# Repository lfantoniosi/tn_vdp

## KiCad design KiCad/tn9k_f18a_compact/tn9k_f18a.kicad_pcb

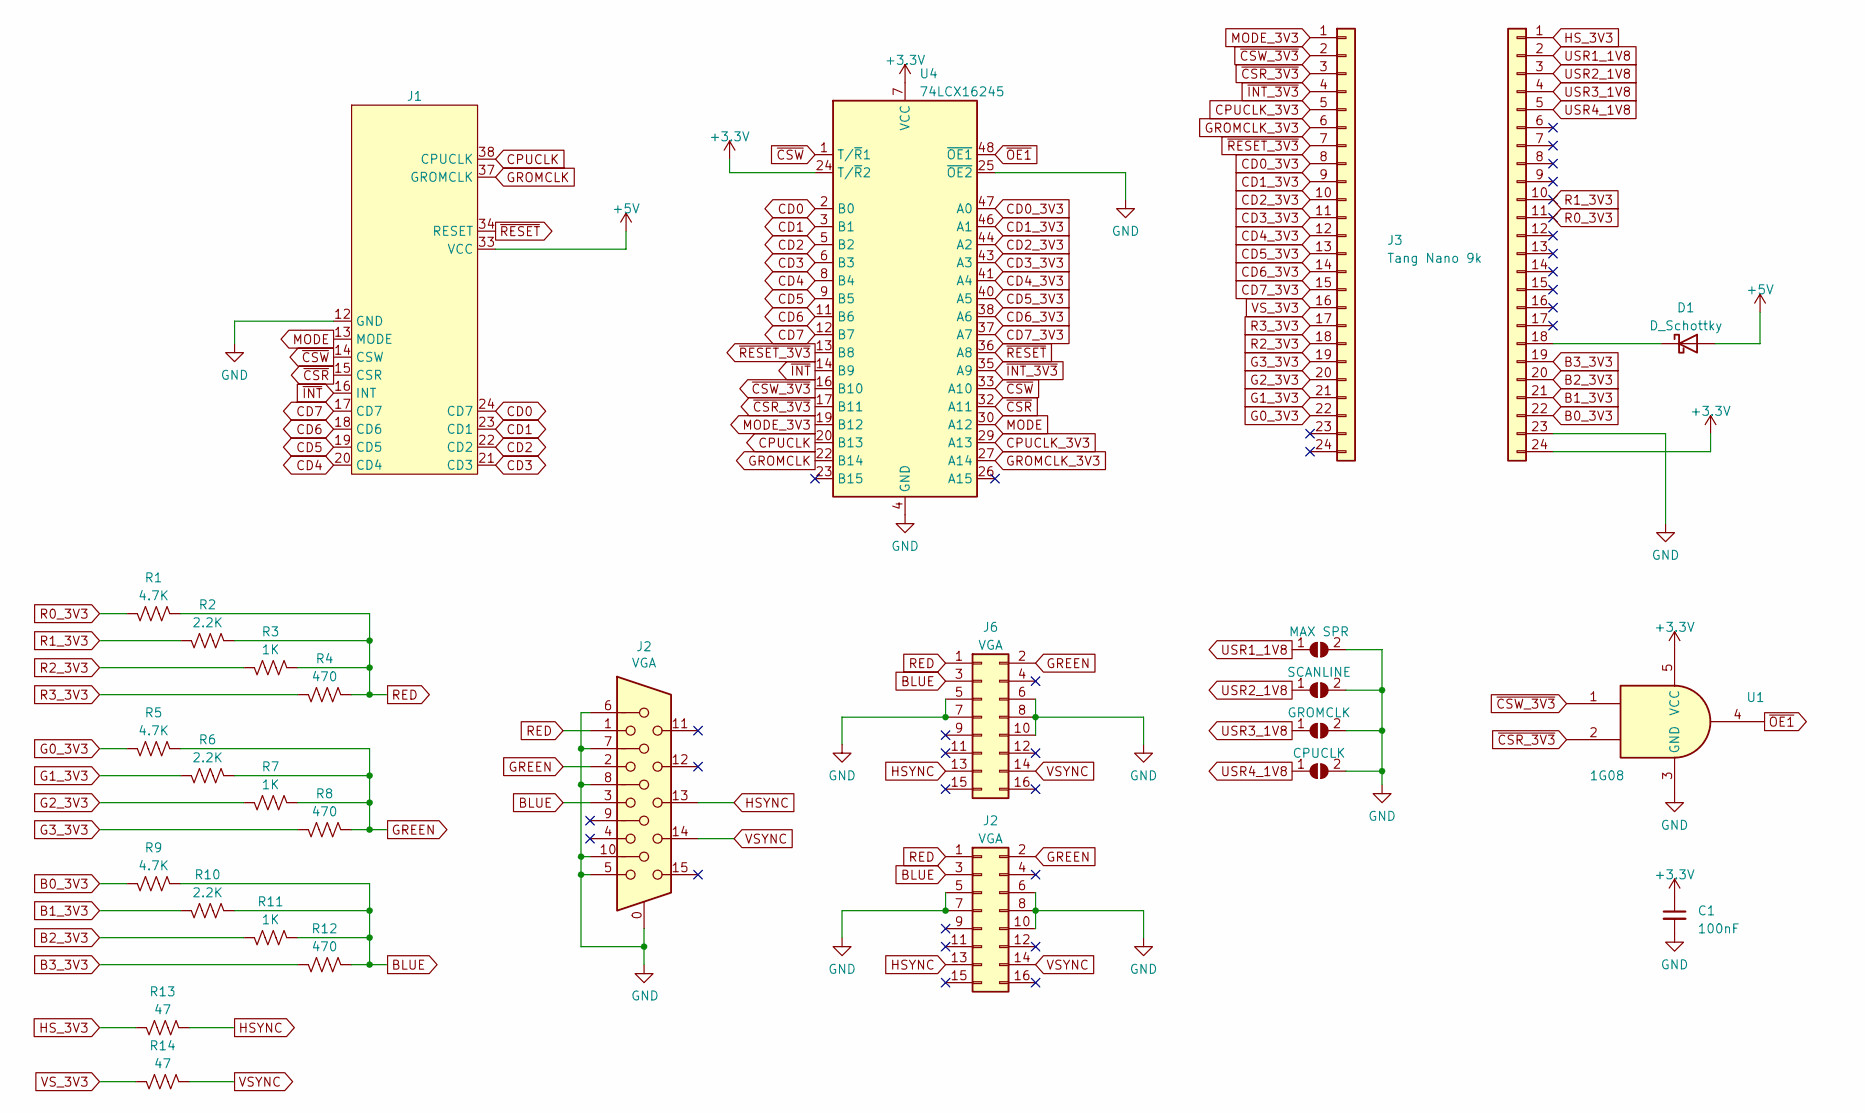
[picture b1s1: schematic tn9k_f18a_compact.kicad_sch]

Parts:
C1: 100nF; C_0603_1608Metric_Pad1.08x0.95mm_HandSolder
D1: D_Schottky; D_SOD-123
J1: TMS99xxA_Replacement
J2: VGA; DSUB-15-HD_Female_Horizontal_P2.29x1.98mm_EdgePinOffset3.03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
J3: Tang Nano 9k; PinSocket_1x24_P2.54mm_Vertical
J4: TN9k/2; PinSocket_1x24_P2.54mm_Vertical
J6: VGA; PinHeader_2x08_P2.54mm_Vertical
JP1: MAX SPR; SolderJumper-2_P1.3mm_Open_RoundedPad1.0x1.5mm
JP2: SCANLINE; SolderJumper-2_P1.3mm_Open_RoundedPad1.0x1.5mm
JP3: GROMCLK; SolderJumper-2_P1.3mm_Open_RoundedPad1.0x1.5mm
JP4: CPUCLK; SolderJumper-2_P1.3mm_Open_RoundedPad1.0x1.5mm
R1, R5, R9: 4.7K; R_0603_1608Metric_Pad0.98x0.95mm_HandSolder
R2, R6, R10: 2.2K; R_0603_1608Metric_Pad0.98x0.95mm_HandSolder
R3, R7, R11: 1K; R_0603_1608Metric_Pad0.98x0.95mm_HandSolder
R4, R8, R12: 470; R_0603_1608Metric_Pad0.98x0.95mm_HandSolder
R13, R14: 47; R_0603_1608Metric_Pad0.98x0.95mm_HandSolder
U1: 1G08; SOT-23-5_HandSoldering
U4: 74LCX16245; TSSOP-48_6.1x12.5mm_P0.5mm

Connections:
+3.3V: C1.1, J4.24, U1.5 (VCC), U4.7 (VCC), U4.18 (VCC), U4.24 (T/~R2), U4.31 (VCC), U4.42 (VCC)
+5V: D1.1 (K), D1.2 (A), J1.33 (VCC), J4.18
B0_3V3: J4.22, R9.2
B1_3V3: J4.21, R10.2
B2_3V3: J4.20, R11.2
B3_3V3: J4.19, R12.2
BLUE: J2.3, J6.3, R9.1, R10.1, R11.1, R12.1; also elsewhere on the board
CD0: J1.24 (CD7), U4.2 (B0)
CD0_3V3: J3.8, U4.47 (A0)
CD1: J1.23 (CD1), U4.3 (B1)
CD1_3V3: J3.9, U4.46 (A1)
CD2: J1.22 (CD2), U4.5 (B2)
CD2_3V3: J3.10, U4.44 (A2)
CD3: J1.21 (CD3), U4.6 (B3)
CD3_3V3: J3.11, U4.43 (A3)
CD4: J1.20 (CD4), U4.8 (B4)
CD4_3V3: J3.12, U4.41 (A4)
CD5: J1.19 (CD5), U4.9 (B5)
CD5_3V3: J3.13, U4.40 (A5)
CD6: J1.18 (CD6), U4.11 (B6)
CD6_3V3: J3.14, U4.38 (A6)
CD7: J1.17 (CD7), U4.12 (B7)
CD7_3V3: J3.15, U4.37 (A7)
CPUCLK: J1.38 (CPUCLK), U4.20 (B13)
CPUCLK_3V3: J3.5, U4.29 (A13)
G0_3V3: J3.22, R5.2
G1_3V3: J3.21, R6.2
G2_3V3: J3.20, R7.2
G3_3V3: J3.19, R8.2
GND: C1.2, J1.12 (GND), J2.0, J2.5, J2.6, J2.7, J2.8, J2.10, J4.23, J6.5, J6.6, J6.7, J6.8, J6.10, JP1.2 (B), JP2.2 (B), JP3.2 (B), JP4.2 (B), U1.3 (GND), U4.4 (GND), U4.10 (GND), U4.15 (GND), U4.21 (GND), U4.25 (~OE2), U4.28 (GND), U4.34 (GND), U4.39 (GND), U4.45 (GND); also elsewhere on the board
GREEN: J2.2, J6.2, R5.1, R6.1, R7.1, R8.1; also elsewhere on the board
GROMCLK: J1.37 (GROMCLK), U4.22 (B14)
GROMCLK_3V3: J3.6, U4.27 (A14)
HSYNC: J2.13, J6.13, R13.1; also elsewhere on the board
HS_3V3: J4.1, R13.2
MODE: J1.13 (MODE), U4.30 (A12)
MODE_3V3: J3.1, U4.19 (B12)
R0_3V3: J4.11, R1.2
R1_3V3: J4.10, R2.2
R2_3V3: J3.18, R3.2
R3_3V3: J3.17, R4.2
RED: J2.1, J6.1, R1.1, R2.1, R3.1, R4.1; also elsewhere on the board
USR1_1V8: J4.2, JP1.1 (A)
USR2_1V8: J4.3, JP2.1 (A)
USR3_1V8: J4.4, JP3.1 (A)
USR4_1V8: J4.5, JP4.1 (A)
VSYNC: J2.14, J6.14, R14.1; also elsewhere on the board
VS_3V3: J3.16, R14.2
~CSR_3V3: J3.3, U1.2, U4.17 (B11)
~CSR: J1.15 (CSR), U4.32 (A11)
~CSW_3V3: J3.2, U1.1, U4.16 (B10)
~CSW: J1.14 (CSW), U4.1 (T/~R1), U4.33 (A10)
~INT_3V3: J3.4, U4.35 (A9)
~INT: J1.16 (INT), U4.14 (B9)
~OE1: U1.4, U4.48 (~OE1)
~RESET_3V3: J3.7, U4.13 (B8)
~RESET: J1.34 (RESET), U4.36 (A8)

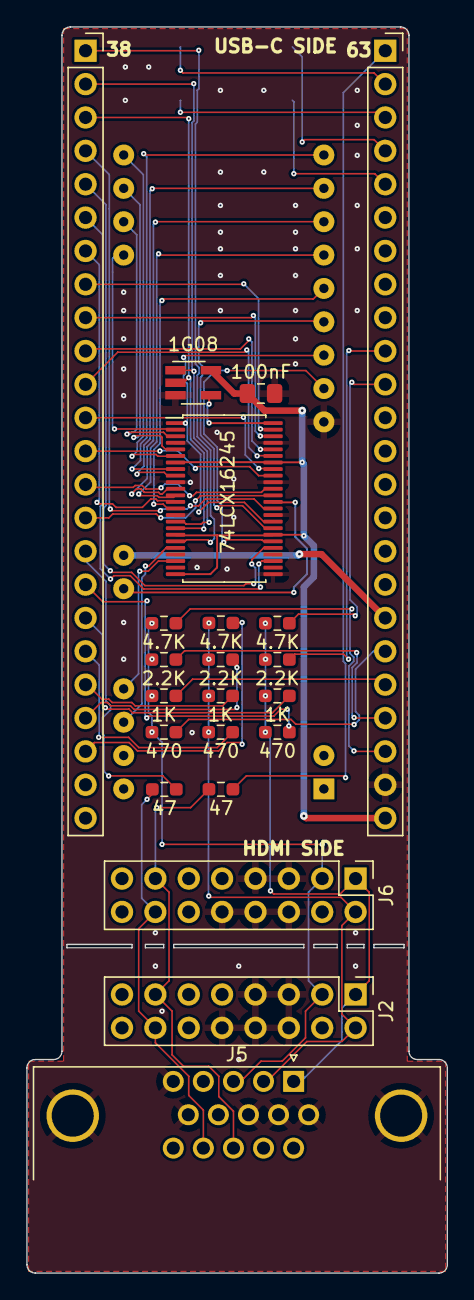
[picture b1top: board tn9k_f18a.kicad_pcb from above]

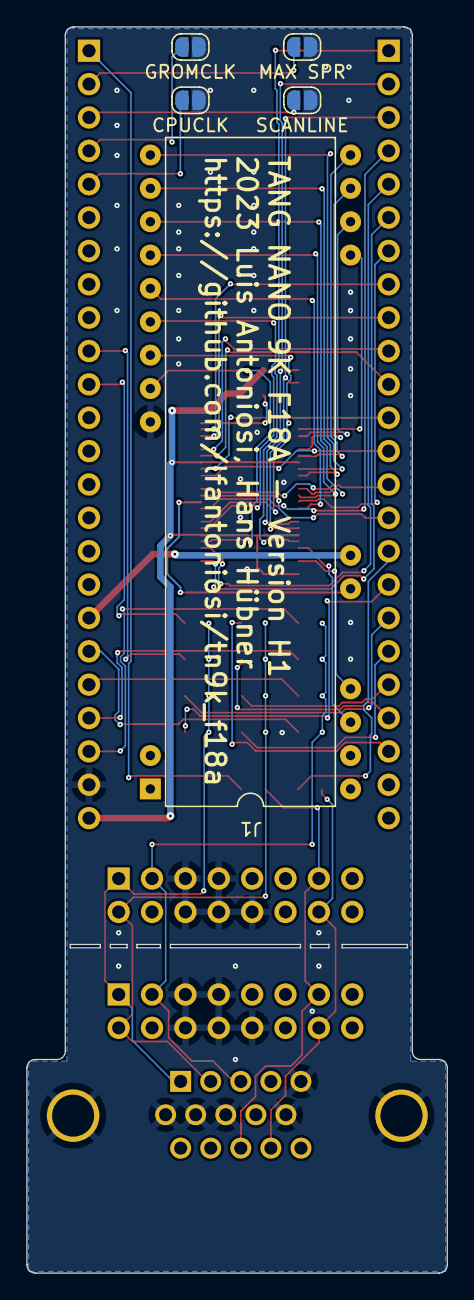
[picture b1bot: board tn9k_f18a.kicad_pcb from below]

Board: 2 copper layers, 32.0 x 94.9 mm, 27 parts (4 on the bottom side), 57 nets.

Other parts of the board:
J5: VGA; DSUB-15-HD_Female_Horizontal_P2.29x1.98mm_EdgePinOffset3.03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

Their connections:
BLUE: J5.3; also elsewhere on the board
GND: J5.0, J5.5, J5.6, J5.7, J5.8, J5.10; also elsewhere on the board
GREEN: J5.2; also elsewhere on the board
HSYNC: J5.13; also elsewhere on the board
RED: J5.1; also elsewhere on the board
VSYNC: J5.14; also elsewhere on the board

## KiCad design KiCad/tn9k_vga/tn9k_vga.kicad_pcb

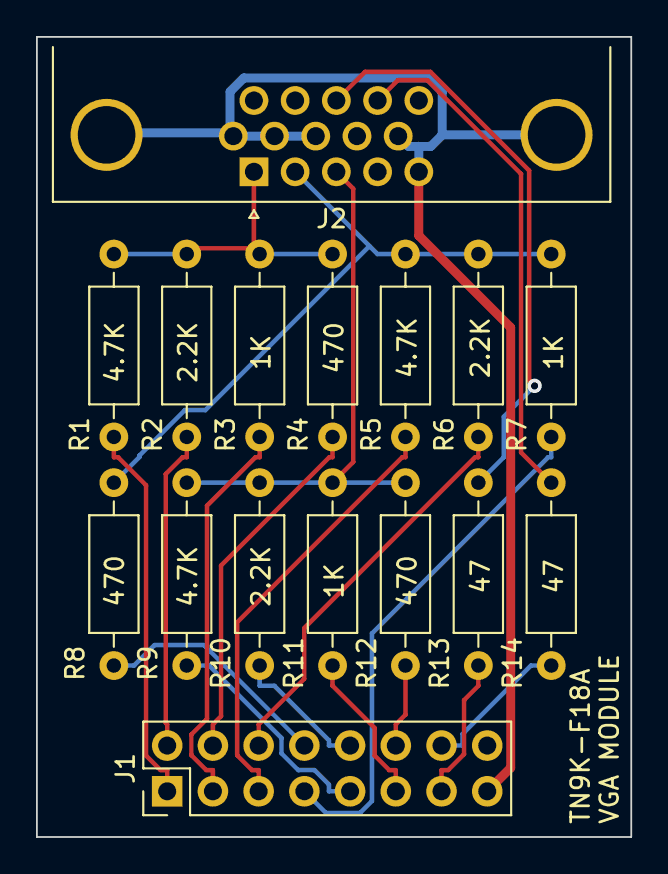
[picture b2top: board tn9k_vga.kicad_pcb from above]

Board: 2 copper layers, 33.0 x 44.5 mm, 16 parts (0 on the bottom side), 20 nets.

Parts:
J1: Conn_02x08_Odd_Even; PinHeader_2x08_P2.54mm_Vertical
J2: DE15_Receptacle_HighDensity_MountingHoles; DSUB-15-HD_Female_Horizontal_P2.29x1.98mm_EdgePinOffset3.03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
R1, R5, R9: 4.7K; R_Axial_DIN0207_L6.3mm_D2.5mm_P10.16mm_Horizontal
R2, R6, R10: 2.2K; R_Axial_DIN0207_L6.3mm_D2.5mm_P10.16mm_Horizontal
R3, R7, R11: 1K; R_Axial_DIN0207_L6.3mm_D2.5mm_P10.16mm_Horizontal
R4, R8, R12: 470; R_Axial_DIN0207_L6.3mm_D2.5mm_P10.16mm_Horizontal
R13, R14: 47; R_Axial_DIN0207_L6.3mm_D2.5mm_P10.16mm_Horizontal

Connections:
B0_3V3: J1.9, R9.2
B1_3V3: J1.10, R10.2
B2_3V3: J1.11, R11.2
B3_3V3: J1.12, R12.2
BLUE: J2.3, R9.1, R10.1, R11.1, R12.1
G0_3V3: J1.5, R5.2
G1_3V3: J1.6, R6.2
G2_3V3: J1.7, R7.2
G3_3V3: J1.8, R8.2
GND: J1.15, J2.0, J2.5, J2.6, J2.7, J2.8, J2.10
GREEN: J2.2, R5.1, R6.1, R7.1, R8.1
HSYNC: J2.13, R13.1
HS_3V3: J1.13, R13.2
R0_3V3: J1.1, R1.2
R1_3V3: J1.2, R2.2
R2_3V3: J1.3, R3.2
R3_3V3: J1.4, R4.2
RED: J2.1, R1.1, R2.1, R3.1, R4.1
VSYNC: J2.14, R14.1
VS_3V3: J1.14, R14.2

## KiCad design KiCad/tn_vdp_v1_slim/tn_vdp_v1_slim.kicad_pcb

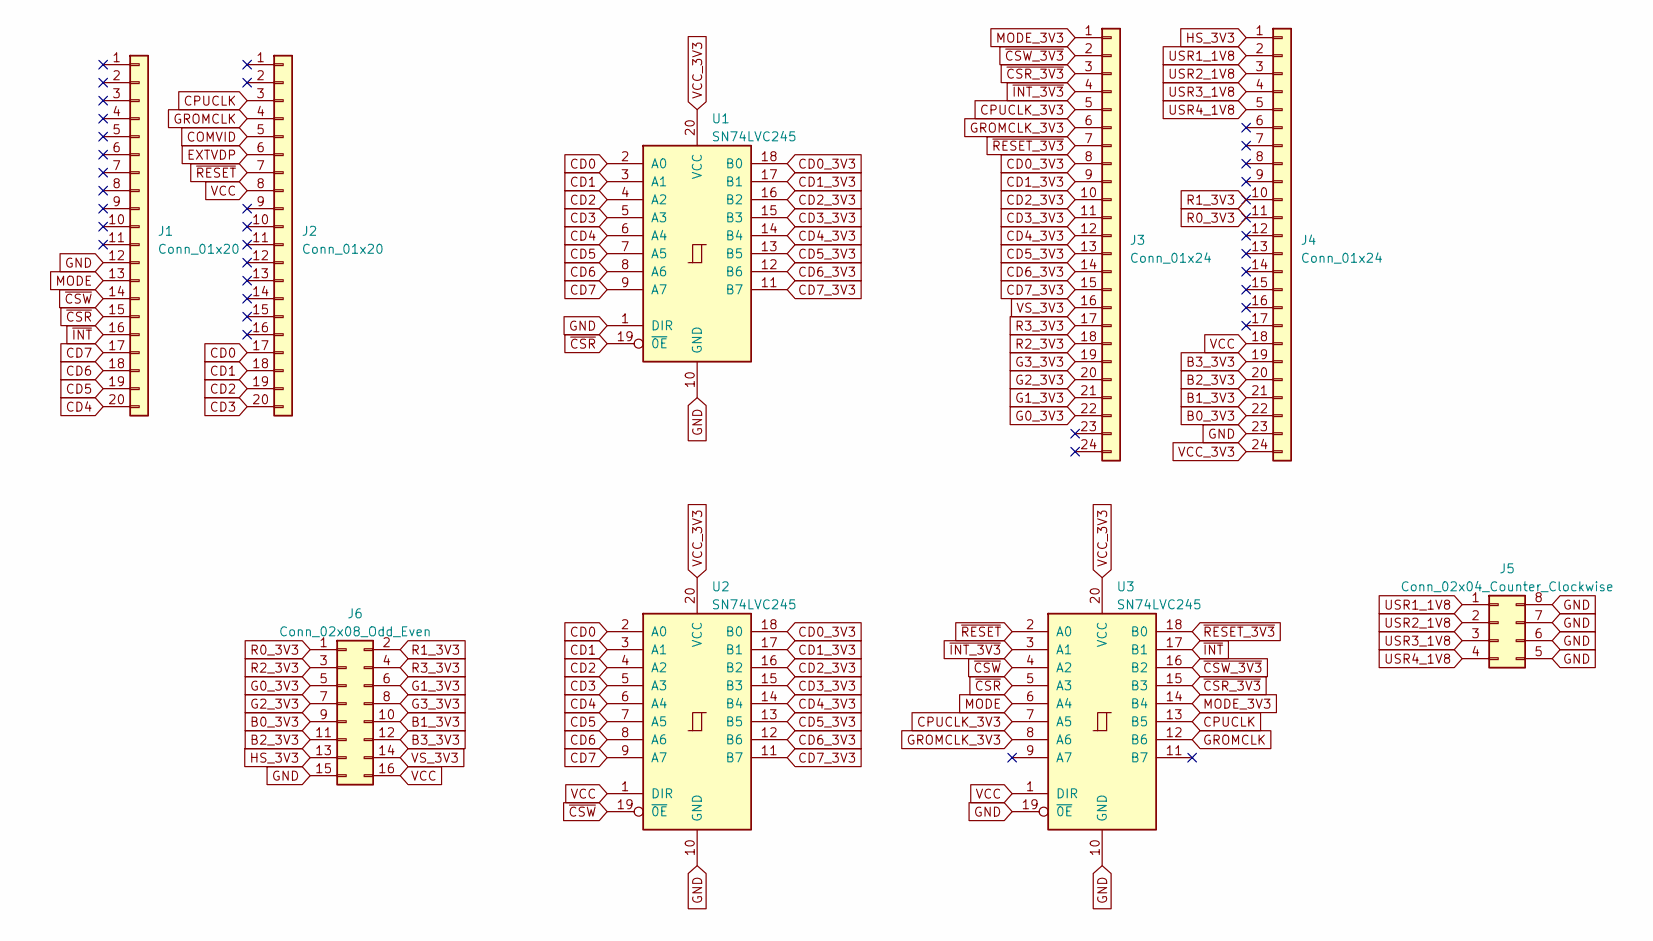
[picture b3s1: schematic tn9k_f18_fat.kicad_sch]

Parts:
J1, J2: Conn_01x20; PinHeader_1x20_P2.54mm_Vertical
J3, J4: Conn_01x24; PinSocket_1x24_P2.54mm_Vertical
J5: Conn_02x04_Counter_Clockwise; SW_DIP_SPSTx04_Slide_6.7x11.72mm_W7.62mm_P2.54mm_LowProfile
J6: Conn_02x08_Odd_Even; PinHeader_2x08_P2.54mm_Horizontal
U1, U2, U3: SN74LVC245; DIP-20_W7.62mm_Socket_LongPads

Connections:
B0_3V3: J4.22, J6.9
B1_3V3: J4.21, J6.10
B2_3V3: J4.20, J6.11
B3_3V3: J4.19, J6.12
CD0: J2.17, U1.2 (A0), U2.2 (A0)
CD0_3V3: J3.8, U1.18 (B0), U2.18 (B0)
CD1: J2.18, U1.3 (A1), U2.3 (A1)
CD1_3V3: J3.9, U1.17 (B1), U2.17 (B1)
CD2: J2.19, U1.4 (A2), U2.4 (A2)
CD2_3V3: J3.10, U1.16 (B2), U2.16 (B2)
CD3: J2.20, U1.5 (A3), U2.5 (A3)
CD3_3V3: J3.11, U1.15 (B3), U2.15 (B3)
CD4: J1.20, U1.6 (A4), U2.6 (A4)
CD4_3V3: J3.12, U1.14 (B4), U2.14 (B4)
CD5: J1.19, U1.7 (A5), U2.7 (A5)
CD5_3V3: J3.13, U1.13 (B5), U2.13 (B5)
CD6: J1.18, U1.8 (A6), U2.8 (A6)
CD6_3V3: J3.14, U1.12 (B6), U2.12 (B6)
CD7: J1.17, U1.9 (A7), U2.9 (A7)
CD7_3V3: J3.15, U1.11 (B7), U2.11 (B7)
COMVID: J2.5
CPUCLK: J2.3, U3.13 (B5)
CPUCLK_3V3: J3.5, U3.7 (A5)
EXTVDP: J2.6
G0_3V3: J3.22, J6.5
G1_3V3: J3.21, J6.6
G2_3V3: J3.20, J6.7
G3_3V3: J3.19, J6.8
GROMCLK: J2.4, U3.12 (B6)
GROMCLK_3V3: J3.6, U3.8 (A6)
HS_3V3: J4.1, J6.13
MODE: J1.13, U3.6 (A4)
MODE_3V3: J3.1, U3.14 (B4)
R0_3V3: J4.11, J6.1
R1_3V3: J4.10, J6.2
R2_3V3: J3.18, J6.3
R3_3V3: J3.17, J6.4
USR1_1V8: J4.2, J5.1
USR2_1V8: J4.3, J5.2
USR3_1V8: J4.4, J5.3
USR4_1V8: J4.5, J5.4
VCC_3V3: J4.24, U1.20 (VCC), U2.20 (VCC), U3.20 (VCC)
VS_3V3: J3.16, J6.14
~CSR_3V3: J3.3, U3.15 (B3)
~CSR: J1.15, U1.19 (~0E), U3.5 (A3)
~CSW_3V3: J3.2, U3.16 (B2)
~CSW: J1.14, U2.19 (~0E), U3.4 (A2)
~INT_3V3: J3.4, U3.3 (A1)
~INT: J1.16, U3.17 (B1)
~RESET_3V3: J3.7, U3.18 (B0)
~RESET: J2.7, U3.2 (A0)

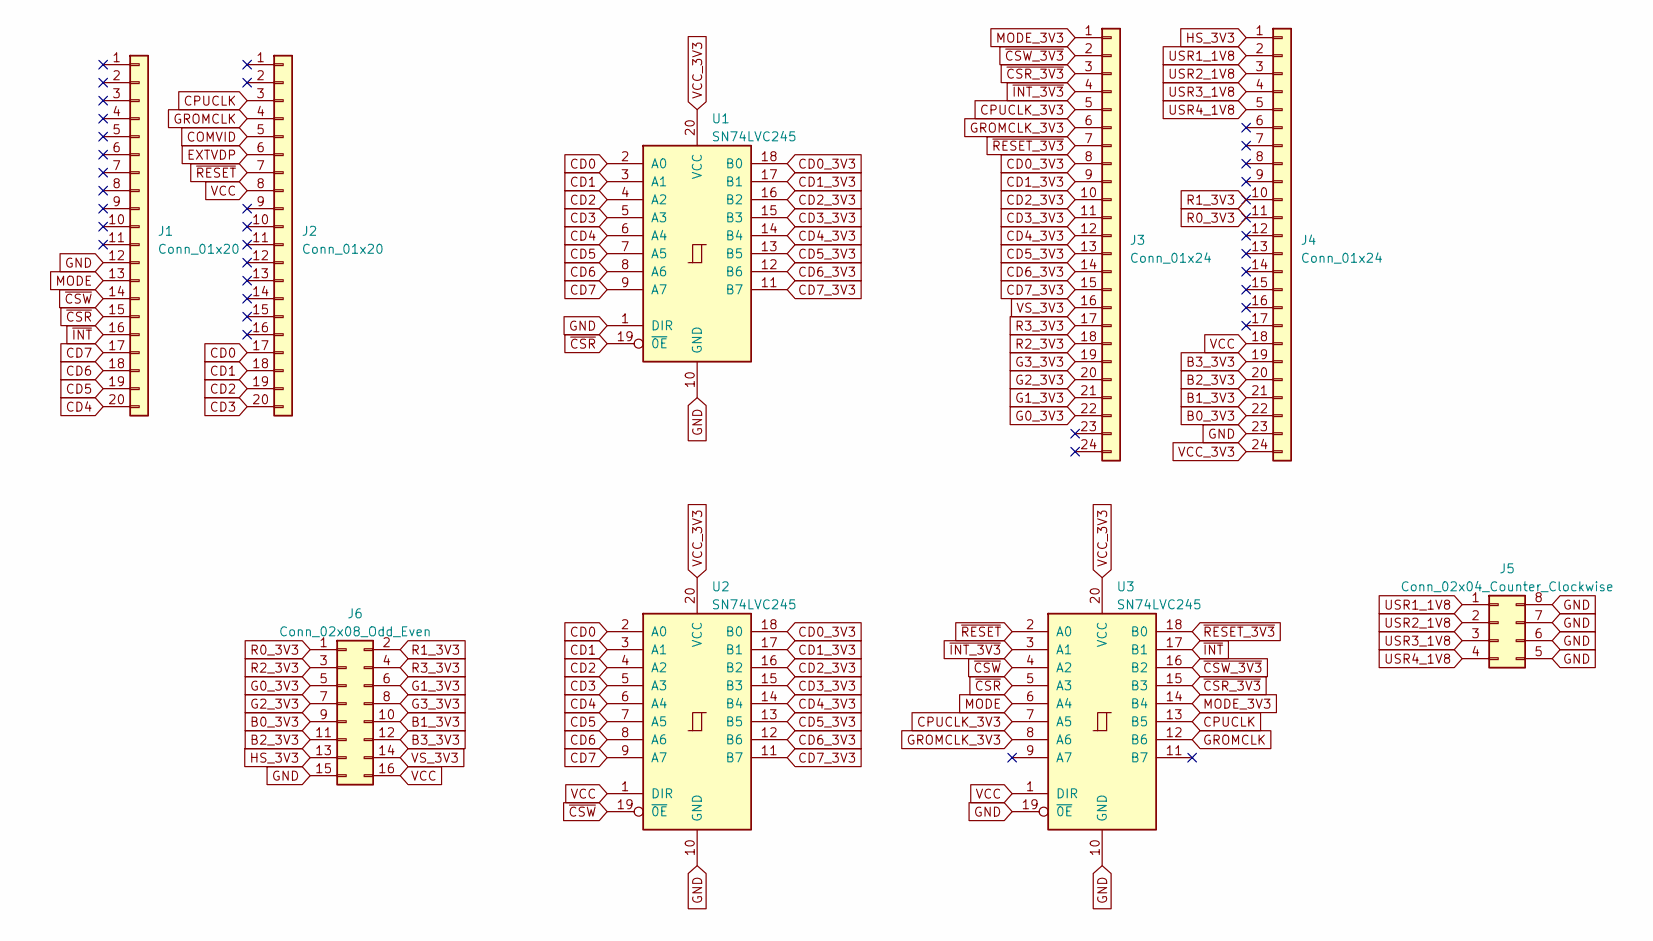
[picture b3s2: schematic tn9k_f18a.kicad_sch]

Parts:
J1, J2: Conn_01x20; PinHeader_1x20_P2.54mm_Vertical
J3, J4: Conn_01x24; PinSocket_1x24_P2.54mm_Vertical
J5: Conn_02x04_Counter_Clockwise; SW_DIP_SPSTx04_Slide_6.7x11.72mm_W7.62mm_P2.54mm_LowProfile
J6: Conn_02x08_Odd_Even; PinHeader_2x08_P2.54mm_Vertical
U1, U2, U3: SN74LVC245; DIP-20_W7.62mm_Socket_LongPads

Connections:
B0_3V3: J4.22, J6.9
B1_3V3: J4.21, J6.10
B2_3V3: J4.20, J6.11
B3_3V3: J4.19, J6.12
CD0: J2.17, U1.2 (A0), U2.2 (A0)
CD0_3V3: J3.8, U1.18 (B0), U2.18 (B0)
CD1: J2.18, U1.3 (A1), U2.3 (A1)
CD1_3V3: J3.9, U1.17 (B1), U2.17 (B1)
CD2: J2.19, U1.4 (A2), U2.4 (A2)
CD2_3V3: J3.10, U1.16 (B2), U2.16 (B2)
CD3: J2.20, U1.5 (A3), U2.5 (A3)
CD3_3V3: J3.11, U1.15 (B3), U2.15 (B3)
CD4: J1.20, U1.6 (A4), U2.6 (A4)
CD4_3V3: J3.12, U1.14 (B4), U2.14 (B4)
CD5: J1.19, U1.7 (A5), U2.7 (A5)
CD5_3V3: J3.13, U1.13 (B5), U2.13 (B5)
CD6: J1.18, U1.8 (A6), U2.8 (A6)
CD6_3V3: J3.14, U1.12 (B6), U2.12 (B6)
CD7: J1.17, U1.9 (A7), U2.9 (A7)
CD7_3V3: J3.15, U1.11 (B7), U2.11 (B7)
COMVID: J2.5
CPUCLK: J2.3, U3.13 (B5)
CPUCLK_3V3: J3.5, U3.7 (A5)
EXTVDP: J2.6
G0_3V3: J3.22, J6.5
G1_3V3: J3.21, J6.6
G2_3V3: J3.20, J6.7
G3_3V3: J3.19, J6.8
GROMCLK: J2.4, U3.12 (B6)
GROMCLK_3V3: J3.6, U3.8 (A6)
HS_3V3: J4.1, J6.13
MODE: J1.13, U3.6 (A4)
MODE_3V3: J3.1, U3.14 (B4)
R0_3V3: J4.11, J6.1
R1_3V3: J4.10, J6.2
R2_3V3: J3.18, J6.3
R3_3V3: J3.17, J6.4
USR1_1V8: J4.2, J5.1
USR2_1V8: J4.3, J5.2
USR3_1V8: J4.4, J5.3
USR4_1V8: J4.5, J5.4
VCC_3V3: J4.24, U1.20 (VCC), U2.20 (VCC), U3.20 (VCC)
VS_3V3: J3.16, J6.14
~CSR_3V3: J3.3, U3.15 (B3)
~CSR: J1.15, U1.19 (~0E), U3.5 (A3)
~CSW_3V3: J3.2, U3.16 (B2)
~CSW: J1.14, U2.19 (~0E), U3.4 (A2)
~INT_3V3: J3.4, U3.3 (A1)
~INT: J1.16, U3.17 (B1)
~RESET_3V3: J3.7, U3.18 (B0)
~RESET: J2.7, U3.2 (A0)

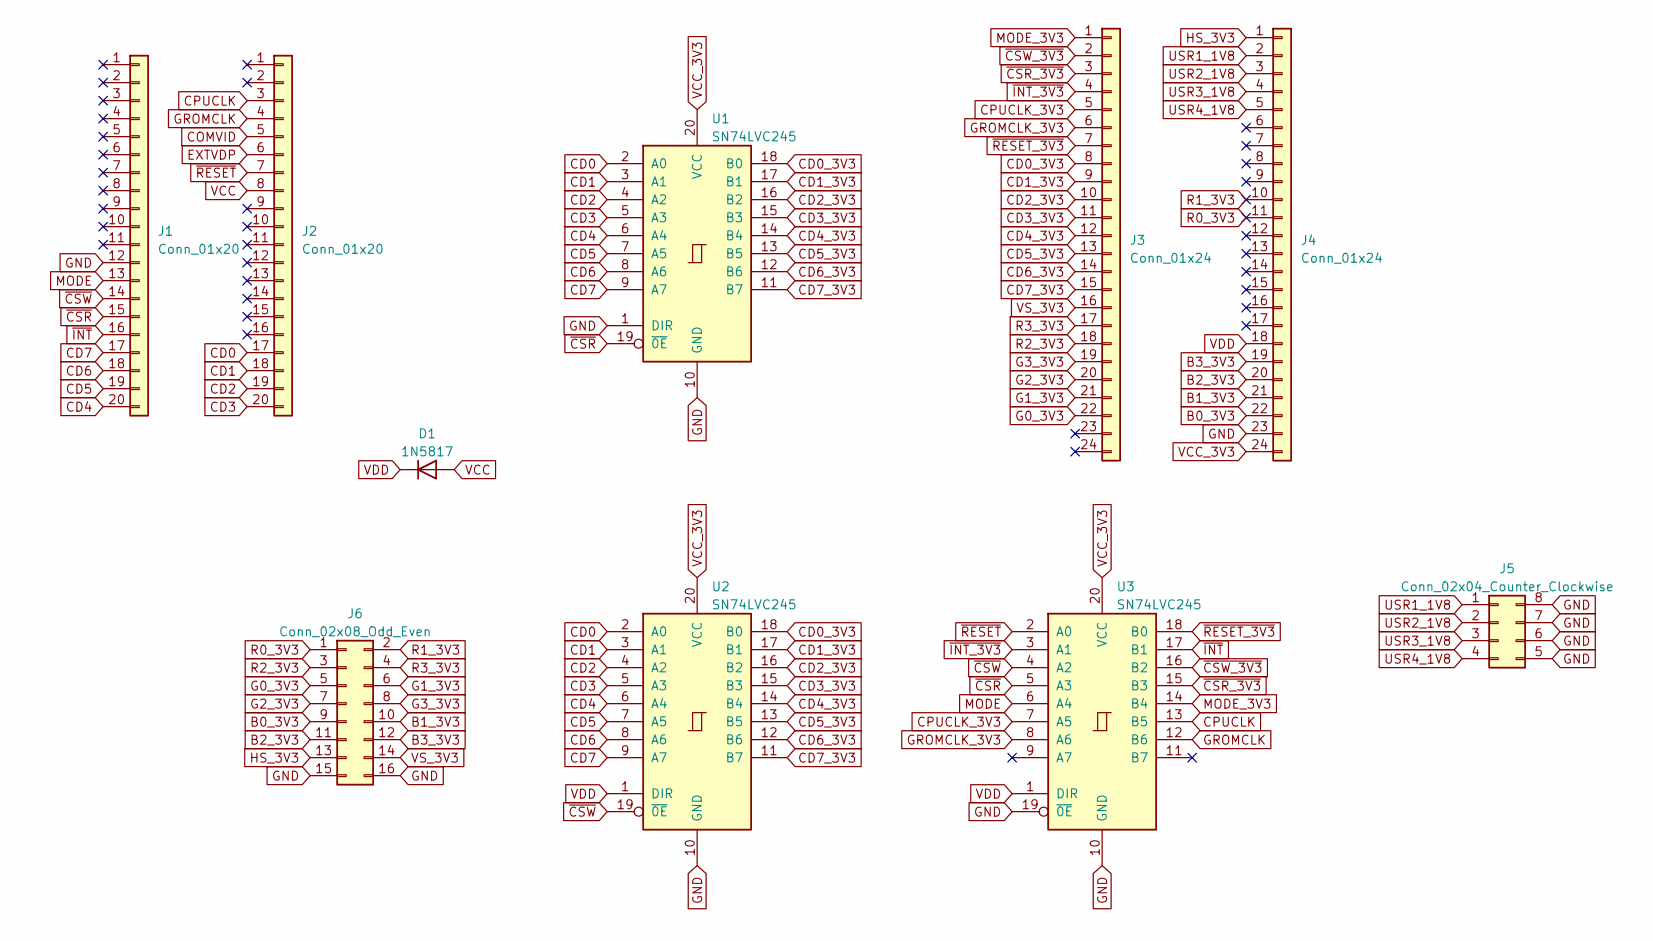
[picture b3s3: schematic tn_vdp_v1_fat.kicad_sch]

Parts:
D1: 1N5817; D_DO-41_SOD81_P10.16mm_Horizontal
J1, J2: Conn_01x20; PinHeader_1x20_P2.54mm_Vertical
J3, J4: Conn_01x24; PinSocket_1x24_P2.54mm_Vertical
J5: Conn_02x04_Counter_Clockwise; SW_DIP_SPSTx04_Slide_6.7x11.72mm_W7.62mm_P2.54mm_LowProfile
J6: Conn_02x08_Odd_Even; PinHeader_2x08_P2.54mm_Horizontal
U1, U2, U3: SN74LVC245; DIP-20_W7.62mm_Socket_LongPads

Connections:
B0_3V3: J4.22, J6.9
B1_3V3: J4.21, J6.10
B2_3V3: J4.20, J6.11
B3_3V3: J4.19, J6.12
CD0: J2.17, U1.2 (A0), U2.2 (A0)
CD0_3V3: J3.8, U1.18 (B0), U2.18 (B0)
CD1: J2.18, U1.3 (A1), U2.3 (A1)
CD1_3V3: J3.9, U1.17 (B1), U2.17 (B1)
CD2: J2.19, U1.4 (A2), U2.4 (A2)
CD2_3V3: J3.10, U1.16 (B2), U2.16 (B2)
CD3: J2.20, U1.5 (A3), U2.5 (A3)
CD3_3V3: J3.11, U1.15 (B3), U2.15 (B3)
CD4: J1.20, U1.6 (A4), U2.6 (A4)
CD4_3V3: J3.12, U1.14 (B4), U2.14 (B4)
CD5: J1.19, U1.7 (A5), U2.7 (A5)
CD5_3V3: J3.13, U1.13 (B5), U2.13 (B5)
CD6: J1.18, U1.8 (A6), U2.8 (A6)
CD6_3V3: J3.14, U1.12 (B6), U2.12 (B6)
CD7: J1.17, U1.9 (A7), U2.9 (A7)
CD7_3V3: J3.15, U1.11 (B7), U2.11 (B7)
COMVID: J2.5
CPUCLK: J2.3, U3.13 (B5)
CPUCLK_3V3: J3.5, U3.7 (A5)
EXTVDP: J2.6
G0_3V3: J3.22, J6.5
G1_3V3: J3.21, J6.6
G2_3V3: J3.20, J6.7
G3_3V3: J3.19, J6.8
GROMCLK: J2.4, U3.12 (B6)
GROMCLK_3V3: J3.6, U3.8 (A6)
HS_3V3: J4.1, J6.13
MODE: J1.13, U3.6 (A4)
MODE_3V3: J3.1, U3.14 (B4)
R0_3V3: J4.11, J6.1
R1_3V3: J4.10, J6.2
R2_3V3: J3.18, J6.3
R3_3V3: J3.17, J6.4
USR1_1V8: J4.2, J5.1
USR2_1V8: J4.3, J5.2
USR3_1V8: J4.4, J5.3
USR4_1V8: J4.5, J5.4
VCC_3V3: J4.24, U1.20 (VCC), U2.20 (VCC), U3.20 (VCC)
VS_3V3: J3.16, J6.14
~CSR_3V3: J3.3, U3.15 (B3)
~CSR: J1.15, U1.19 (~0E), U3.5 (A3)
~CSW_3V3: J3.2, U3.16 (B2)
~CSW: J1.14, U2.19 (~0E), U3.4 (A2)
~INT_3V3: J3.4, U3.3 (A1)
~INT: J1.16, U3.17 (B1)
~RESET_3V3: J3.7, U3.18 (B0)
~RESET: J2.7, U3.2 (A0)

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
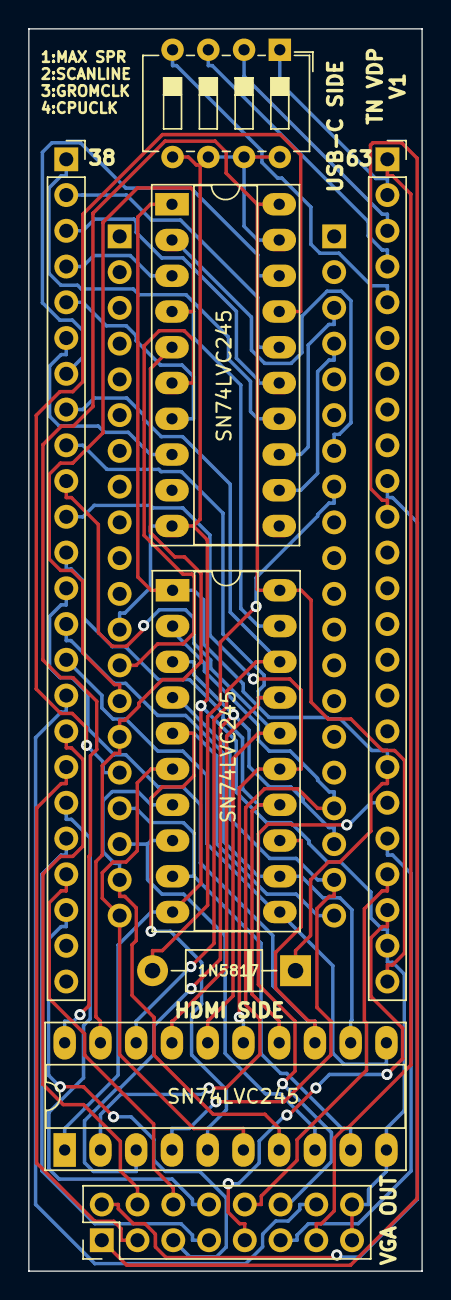
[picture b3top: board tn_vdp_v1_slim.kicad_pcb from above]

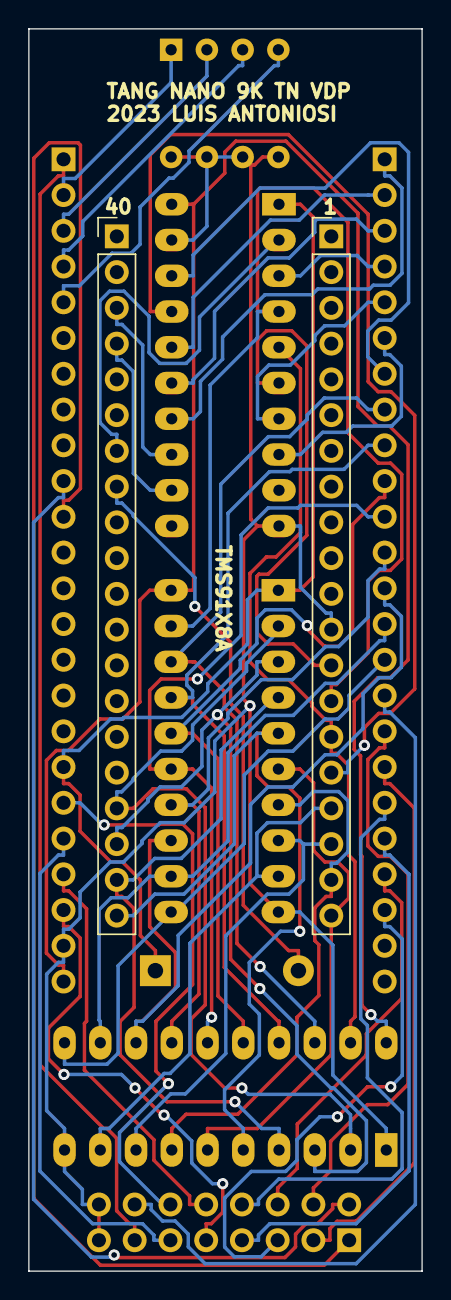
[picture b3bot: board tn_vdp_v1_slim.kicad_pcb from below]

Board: 2 copper layers, 27.9 x 88.3 mm, 10 parts (2 on the bottom side), 52 nets.
